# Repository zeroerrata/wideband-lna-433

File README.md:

<p align="center">
  <a href="https://zeroerrata.eu"><picture>
    <source media="(prefers-color-scheme: dark)" srcset="images/zeroerrata-logo-dark.png">
    
  </picture></a>
</p>

<h1 align="center">Wideband LNA 0.1-3 GHz with a 433 MHz SAW filter</h1>

<p align="center"><b>Low-noise amplifier for SDR receivers: SMA in, SMA out, 0.1-3 GHz, with a switchable 433.92 MHz SAW filter.</b></p>

## About

A small RF front end for software-defined radio receivers. A slide switch selects either the wideband path (0.1-3 GHz) or a 433.92 MHz SAW filter in front of the low-noise amplifier, so the same board serves as a general-purpose LNA and as a narrowband ISM-band preamplifier. It is powered from USB-C (5 V, power only) or through the RF output coax from the receiver's bias-tee (3.3-5 V); the two supplies are OR-ed by a Schottky pair, so it works on the bench and at the antenna mast.

The RF lines are 50-ohm grounded coplanar waveguide without solder mask on a 4-layer board with ENIG finish, fenced by ground vias, with tapered launches into edge-mount SMA connectors.

## Features

- Qorvo SPF5043Z LNA: NF 0.6-0.84 dB up to 2.2 GHz, gain about 23.5 dB at 0.1 GHz falling to about 10 dB at 3 GHz, OIP3 33-35 dBm
- Switchable RF360 B3760 SAW filter, 433.92 MHz: 320 kHz pass band (about 0.7 MHz at -3 dB), 1.9 dB insertion loss, with its matching network
- Two Skyworks AS179-92LF SPDT switches in series around the filter: about 50 dB leakage suppression, a LED for each mode
- Powered by USB-C 5 V or by bias-tee over the RF OUT coax (3.3-5 V)
- 50-ohm grounded coplanar waveguide (0.345 mm track, 0.3 mm gap, no solder mask), via fences, edge-launch SMA
- Hand-solderable: SOT-343 / SOT-363, 0402 on the RF path, 0603 elsewhere (the SAW needs hot air or a hot plate)

## Specifications

| | |
|---|---|
| Board | 56.0 x 34.0 mm, 4 copper layers, 1.6 mm |
| Finish | ENIG |
| Parts | 46 |
| Release | rev 3, 2026-11-27 |
| Frequency | 0.1-3 GHz (wideband) or 433.92 MHz (SAW) |
| RF connectors | 2 x edge-launch SMA, 50 ohm |
| Supply | USB-C 5 V or bias-tee 3.3-5 V on RF OUT |
| Stackup | 4 layers, 1.6 mm, outer copper 1 oz; RF on the top layer over a solid ground plane |

## Performance (simulated)

RF cascade of the whole board between 50-ohm ports: the routed lines on the real stackup, the switches, coupling and bias parts, the SMA launches. The LNA is modelled from its data-sheet curves, the SAW filter as a behavioural band-pass with its data-sheet insertion loss; a prediction, not a measurement.

| Path | Frequency | Gain | Noise figure | Input match (S11) |
|---|---|---|---|---|
| Wideband | 0.1 GHz | 22.3 dB | 1.25 dB | -10.0 dB |
| Wideband | 433.92 MHz | 19.6 dB | 1.34 dB | -13.2 dB |
| Wideband | 0.9 GHz | 16.6 dB | 1.51 dB | -13.9 dB |
| Wideband | 2.2 GHz | 9.7 dB | 2.17 dB | -14.0 dB |
| Wideband | 3 GHz | 7.0 dB | 2.72 dB | -13.3 dB |
| 433 MHz SAW | 433.77-434.07 MHz | 16.9-17.8 dB | 3.2-3.6 dB | -17.0 dB |

- Over part tolerances (Monte Carlo, 200 draws) every band check holds: wideband gain >= 6 dB, NF <= 3 dB, S11 <= -9 dB over 0.1-3 GHz; SAW path gain >= 14 dB (16.9 dB), NF <= 5.5 dB (3.6 dB) in the passband.
- Rejection of the SAW path relative to 433.92 MHz (data-sheet minimum of the filter): about 31 dB at 430 MHz, 21 dB at 437 MHz, 40-46 dB at 400 / 470 MHz, 51-55 dB from 868 MHz to 2.4 GHz, where the isolation of the two switches, not the filter, sets it.
- The data-sheet model of the LNA has no phase information; its stability factor dips below 1 near the edges of the sweep (mu 0.79), so check the stability with a VNA on the first boards.

## Renders

| Top | Bottom | Low |
|---|---|---|
|  |  |  |

## Files

| Folder | Contents |
|---|---|
| [`kicad/`](kicad) | KiCad 10 project: schematic, board, design rules, project libraries |
| [`docs/`](docs) | [schematic.pdf](docs/schematic.pdf), [board_layers.pdf](docs/board_layers.pdf), [assembly_top.pdf](docs/assembly_top.pdf) |
| [`fabrication/`](fabrication) | Gerber and drill files (zip), bill of materials, pick-and-place |
| [`images/`](images) | renders and copper layer pictures |
| [`analysis/`](analysis) | simulation and analysis results: bringup, dfm, retpath, sparam, thermal |

## Verification

- 50-ohm RF lines checked by a field solver: 12 RF nets at 50.0-51.6 ohm
- RF chain cascade (gain, noise figure, match) and Monte Carlo over part tolerances: see analysis/sparam
- Thermal map, return paths of the RF nets and a reflow balance check: see analysis/
- Every result is a prediction from design data; the board has not been measured unless stated.

## How to order

1. Upload `fabrication/gerbers_drill.zip` to your PCB fab; the stackup and finish are in the specifications above.
2. For assembly, use `fabrication/bom_jlcpcb.csv` and `fabrication/cpl_jlcpcb.csv` (JLCPCB format) or the KiCad-format `bom.csv` / `pos.csv`.
3. Check part stock and the footprints against the current data sheets before you order.

## Known issues

Found by the design review of this release; boards built from these files carry them:

- Reflow balance: from rev 3 the small ground pads connect through thermal reliefs; nine 0402 / 0603 parts remain at warning level in the reflow check, so use a profile with a 60-90 s soak at 150-180 C and inspect them.
- Parts: the B3760 SAW filter is not stocked by JLCPCB / LCSC (solder it by hand or consign it), and the AS179-92LF switches had little authorised stock in 2026. Check both before ordering.

## Notes

- The renders show the ZeroErrata house look; from rev 3 the fabrication package specifies it too: matte black solder mask, white silkscreen, ENIG.
- The SAW filter has its pads under the body: solder it with hot air or a hot plate.
- Rev 3 uses the B3760 SAW filter instead of the B3790 (obsolete at one distributor): 1.7 dB lower insertion loss and noise figure, a wider pass band (320 kHz instead of about 120 kHz) and less rejection within about 10 MHz of the carrier.

## Licence

Released under the [CERN Open Hardware Licence Version 2 - Permissive](LICENSE) (CERN-OHL-P-2.0): use, modify, make and sell it, also commercially. Provided as is, without warranty.

---

<p align="center">
  Designed by <a href="https://zeroerrata.eu"><b>ZeroErrata</b></a>: PCB design, verified before it is ordered.<br>
  <a href="https://zeroerrata.eu">zeroerrata.eu</a> · <a href="mailto:hello@zeroerrata.eu">hello@zeroerrata.eu</a>
</p>

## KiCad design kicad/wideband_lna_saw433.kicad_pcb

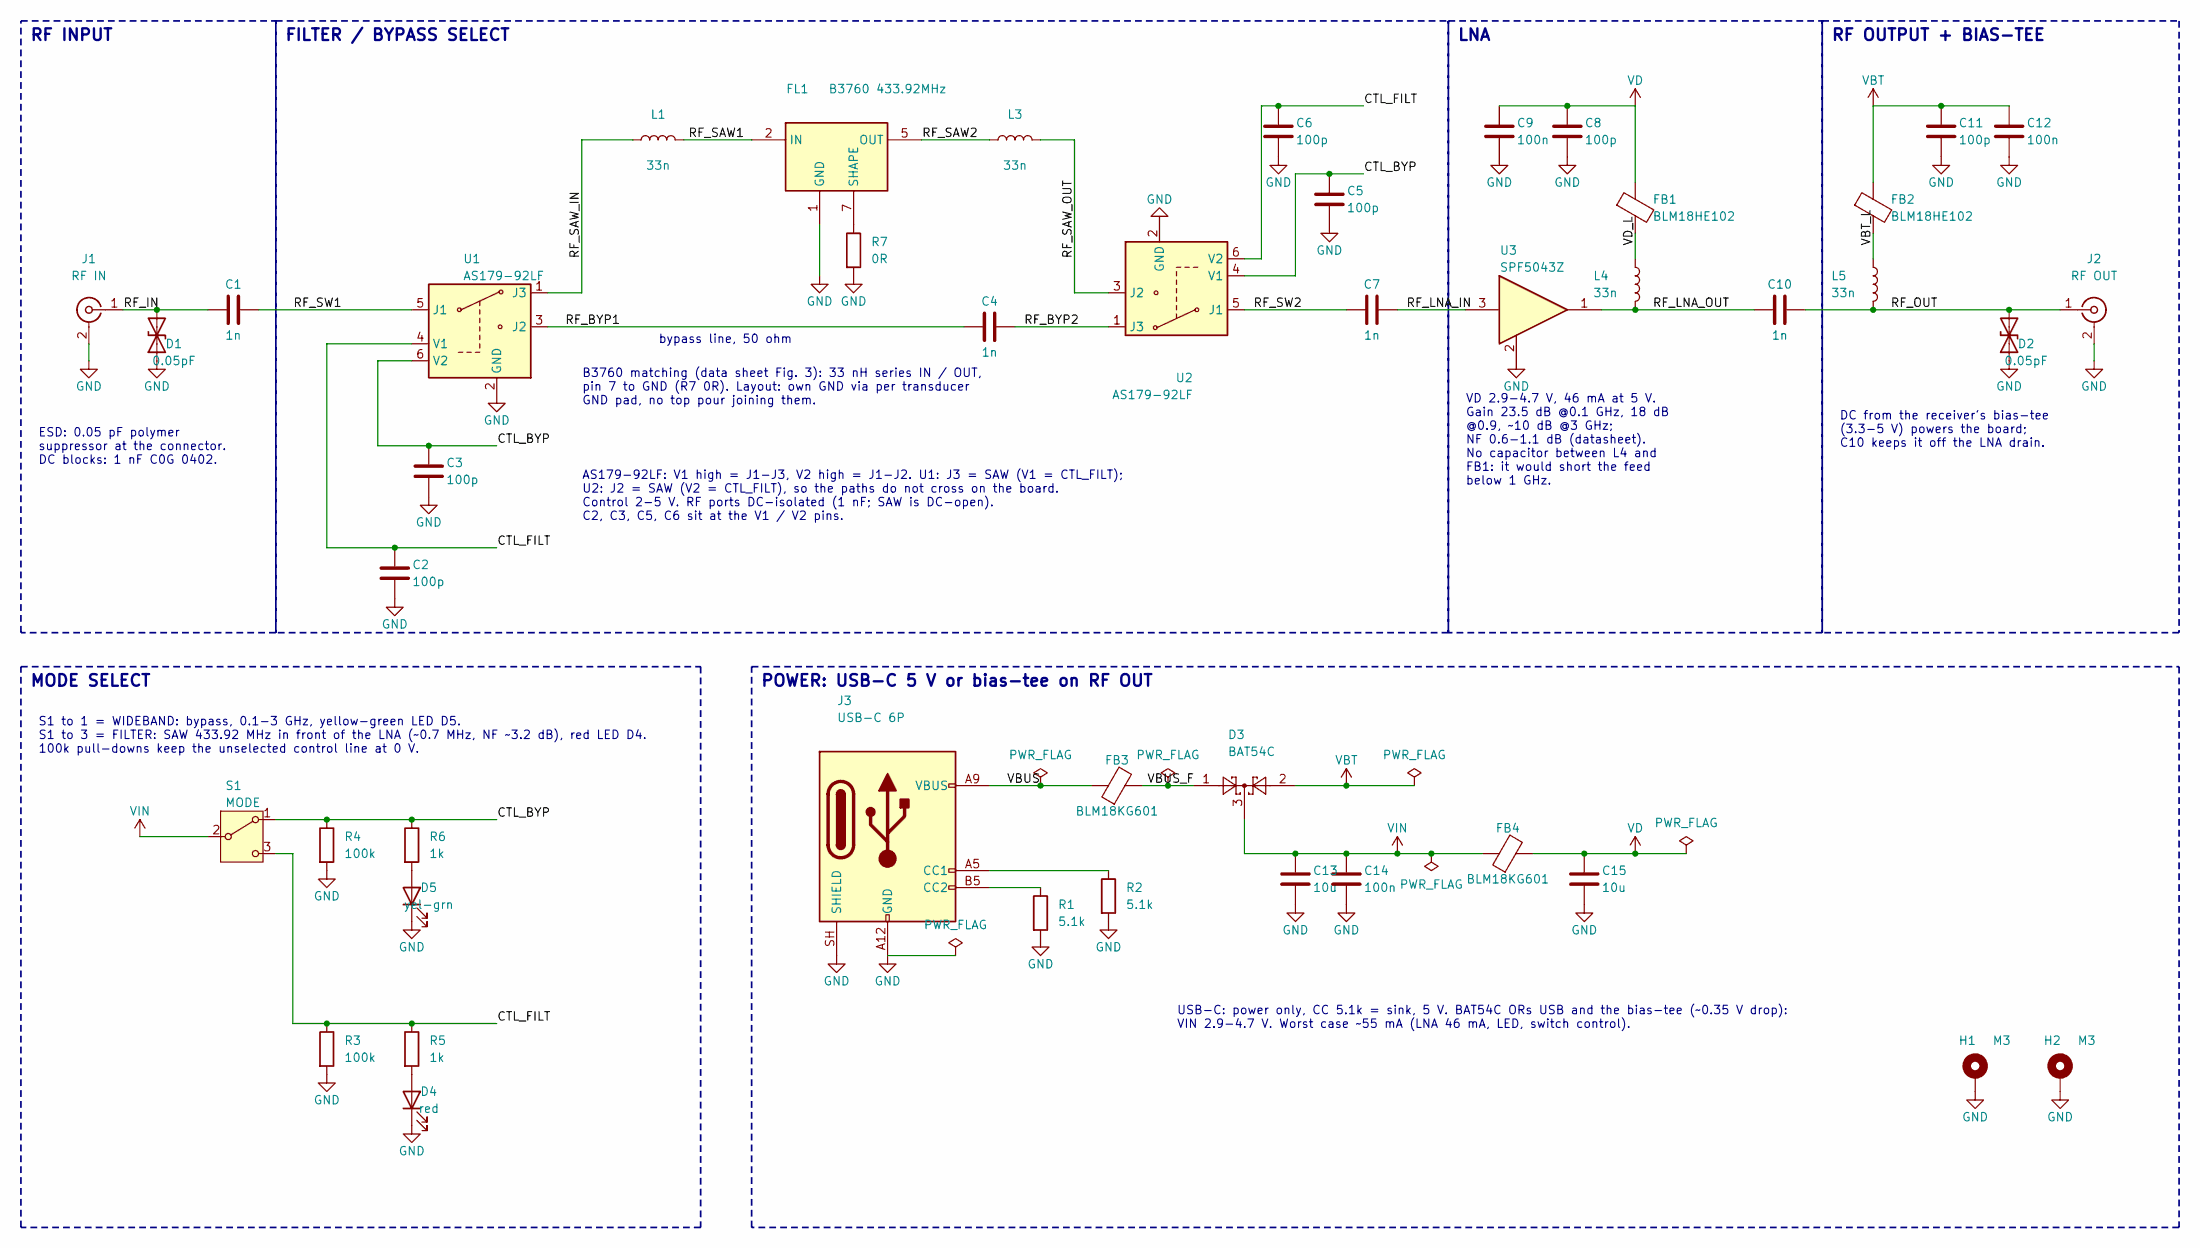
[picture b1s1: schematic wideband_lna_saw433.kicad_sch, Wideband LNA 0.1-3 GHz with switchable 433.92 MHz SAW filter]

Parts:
C1, C4, C7, C10: 1n; C_0402_1005Metric; MPN GRM1555C1H102JA01D; LCSC C76947
C2, C3, C5, C6, C8, C11: 100p; C_0402_1005Metric; MPN GRM1555C1H101JA01D; LCSC C77177
C9, C12, C14: 100n; C_0603_1608Metric; MPN CC0603KRX7R9BB104; LCSC C14663
C13, C15: 10u; C_0603_1608Metric; MPN CL10A106KP8NNNC; LCSC C19702
D1, D2: 0.05pF; D_0402_1005Metric; MPN BPESD0402-05ST; LCSC C316059
D3: BAT54C; SOT-23; MPN BAT54C,215; LCSC C37704
D4: red; LED_0603_1608Metric; MPN KT-0603R; LCSC C2286
D5: yel-grn; LED_0603_1608Metric; MPN XL-1608SYGC-06; LCSC C965805
FB1, FB2: BLM18HE102; L_0603_1608Metric; MPN BLM18HE102SN1D; LCSC C85828
FB3, FB4: BLM18KG601; L_0603_1608Metric; MPN BLM18KG601SN1D; LCSC C85833
FL1: B3760 433.92MHz; QCC8B_3.8x3.8mm; MPN B39431B3760Z810
H1, H2: M3; MountingHole_3.2mm_M3_Pad_Via
J1: RF IN; SMA_Molex_73251-1150_EdgeMount_PB; MPN 73251-1150; LCSC C841205
J2: RF OUT; SMA_Molex_73251-1150_EdgeMount_PB; MPN 73251-1150; LCSC C841205
J3: USB-C 6P; USB_C_Receptacle_ShouHan_TYPE-C-6P; MPN TYPE-C 6P; LCSC C456012
L1, L3, L4, L5: 33n; L_0402_1005Metric; MPN LQW15AN33NG00D; LCSC C113114
R1, R2: 5.1k; R_0603_1608Metric; MPN 0603WAF5101T5E; LCSC C23186
R3, R4: 100k; R_0603_1608Metric; MPN 0603WAF1003T5E; LCSC C25803
R5, R6: 1k; R_0603_1608Metric; MPN 0603WAF1001T5E; LCSC C21190
R7: 0R; L_0402_1005Metric; MPN 0402WGF0000TCE; LCSC C17168
S1: MODE; SW_SPDT_MSK12C02; MPN MSK12C02; LCSC C431540
U1, U2: AS179-92LF; SOT-363_SC-70-6; MPN AS179-92LF; LCSC C83422
U3: SPF5043Z; SOT-343_Qorvo_SPF5043Z; MPN SPF5043Z; LCSC C470902

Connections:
/CTL_BYP: C3.1, C5.1, R4.1, R6.1, S1.1 (A), U1.6 (V2), U2.4 (V1)
/CTL_FILT: C2.1, C6.1, R3.1, R5.1, S1.3 (C), U1.4 (V1), U2.6 (V2)
/RF_BYP1: C4.1, U1.3 (J2)
/RF_BYP2: C4.2, U2.1 (J3)
/RF_IN: C1.1, D1.2 (A2), J1.1 (In)
/RF_LNA_IN: C7.2, U3.3 (RFIN)
/RF_LNA_OUT: C10.1, L4.2, U3.1 (RFOUT/VD)
/RF_OUT: C10.2, D2.2 (A2), J2.1 (In), L5.2
/RF_SAW1: FL1.2 (IN), L1.2
/RF_SAW2: FL1.5 (OUT), L3.1
/RF_SAW_IN: L1.1, U1.1 (J3)
/RF_SAW_OUT: L3.2, U2.3 (J2)
/RF_SW1: C1.2, U1.5 (J1)
/RF_SW2: C7.1, U2.5 (J1)
/VBT_L: FB2.2, L5.1
/VBUS: FB3.1, J3.A9 (VBUS), J3.B9 (VBUS)
/VBUS_F: D3.1, FB3.2
/VD_L: FB1.2, L4.1
GND: C2.2, C3.2, C5.2, C6.2, C8.2, C9.2, C11.2, C12.2, C13.2, C14.2, C15.2, D1.1 (A1), D2.1 (A1), D4.1 (K), D5.1 (K), FL1.1 (GND), FL1.3 (GND), FL1.4 (GND), FL1.6 (GND), FL1.8 (GND), H1.1, H2.1, J1.2 (Ext), J2.2 (Ext), J3.A12 (GND), J3.B12 (GND), J3.SH (SHIELD), R1.2, R2.2, R3.2, R4.2, R7.2, U1.2 (GND), U2.2 (GND), U3.2 (GND), U3.4 (GND)
unnamed: D4.2 (A), R5.2
unnamed: D5.2 (A), R6.2
unnamed: FL1.7 (SHAPE), R7.1
unnamed: J3.A5 (CC1), R2.1
unnamed: J3.B5 (CC2), R1.1
VBT: C11.1, C12.1, D3.2, FB2.1
VD: C8.1, C9.1, C15.1, FB1.1, FB4.2
VIN: C13.1, C14.1, D3.3, FB4.1, S1.2 (B)

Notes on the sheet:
RF INPUT
ESD: 0.05 pF polymer suppressor at the connector. DC blocks: 1 nF C0G 0402.
FILTER / BYPASS SELECT
bypass line, 50 ohm
B3760 matching (data sheet Fig. 3): 33 nH series IN / OUT, pin 7 to GND (R7 0R). Layout: own GND via per transducer GND pad, no top pour joining them.
AS179-92LF: V1 high = J1-J3, V2 high = J1-J2. U1: J3 = SAW (V1 = CTL_FILT); U2: J2 = SAW (V2 = CTL_FILT), so the paths do not cross on the board. Control 2-5 V. RF ports DC-isolated (1 nF; SAW is DC-open). C2, C3, C5, C6 sit at the V1 / V2 pins.
LNA
VD 2.9-4.7 V, 46 mA at 5 V. Gain 23.5 dB @0.1 GHz, 18 dB @0.9, ~10 dB @3 GHz; NF 0.6-1.1 dB (datasheet). No capacitor between L4 and FB1: it would short the feed below 1 GHz.
RF OUTPUT + BIAS-TEE
DC from the receiver's bias-tee (3.3-5 V) powers the board; C10 keeps it off the LNA drain.
MODE SELECT
S1 to 1 = WIDEBAND: bypass, 0.1-3 GHz, yellow-green LED D5. S1 to 3 = FILTER: SAW 433.92 MHz in front of the LNA (~0.7 MHz, NF ~3.2 dB), red LED D4. 100k pull-downs keep the unselected control line at 0 V.
POWER: USB-C 5 V or bias-tee on RF OUT
USB-C: power only, CC 5.1k = sink, 5 V. BAT54C ORs USB and the bias-tee (~0.35 V drop): VIN 2.9-4.7 V. Worst case ~55 mA (LNA 46 mA, LED, switch control).

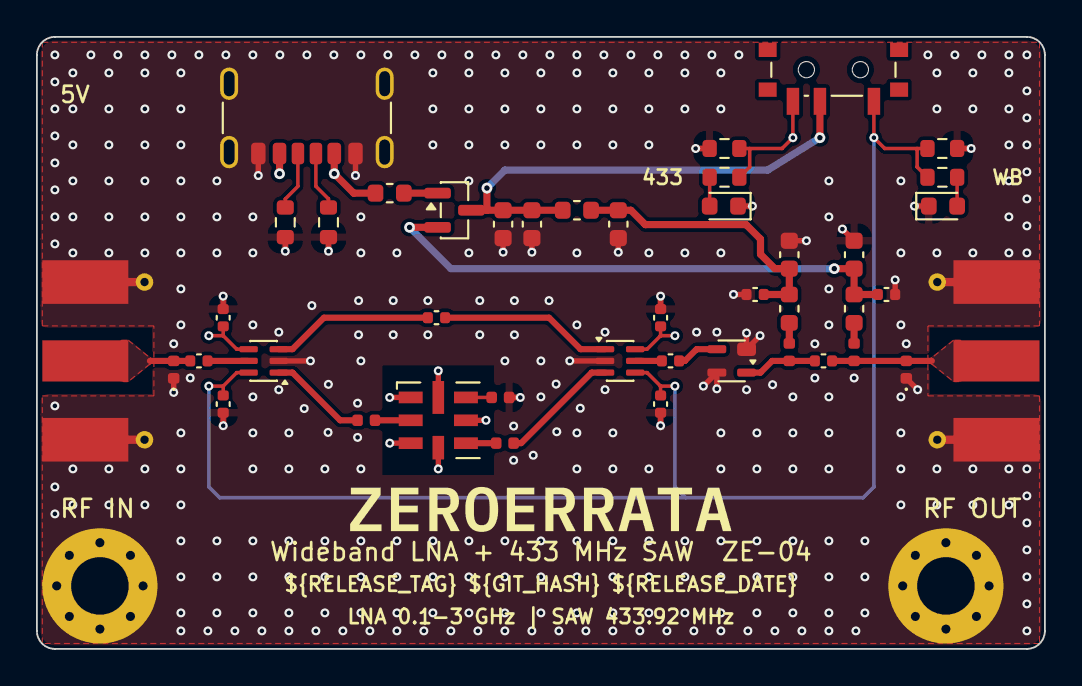
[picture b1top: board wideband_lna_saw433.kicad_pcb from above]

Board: 4 copper layers, 56.0 x 34.0 mm, 46 parts (0 on the bottom side), 27 nets.

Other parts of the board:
LOGO1: ZeroErrata logo; ZeroErrata_wordmark_2.5mm

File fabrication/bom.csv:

"Designator","Value","Footprint","Quantity","Manufacturer","MPN","LCSC Part #"
"C1,C4,C7,C10","1n","Capacitor_SMD:C_0402_1005Metric","4","Murata","GRM1555C1H102JA01D","C76947"
"C2,C3,C5,C6,C8,C11","100p","Capacitor_SMD:C_0402_1005Metric","6","Murata","GRM1555C1H101JA01D","C77177"
"C9,C12,C14","100n","Capacitor_SMD:C_0603_1608Metric","3","YAGEO","CC0603KRX7R9BB104","C14663"
"C13,C15","10u","Capacitor_SMD:C_0603_1608Metric","2","Samsung","CL10A106KP8NNNC","C19702"
"D1,D2","0.05pF","Diode_SMD:D_0402_1005Metric","2","BORN","BPESD0402-05ST","C316059"
"D3","BAT54C","Package_TO_SOT_SMD:SOT-23","1","Nexperia","BAT54C,215","C37704"
"D4","red","LED_SMD:LED_0603_1608Metric","1","KENTO","KT-0603R","C2286"
"D5","yel-grn","LED_SMD:LED_0603_1608Metric","1","XINGLIGHT","XL-1608SYGC-06","C965805"
"FB1,FB2","BLM18HE102","Inductor_SMD:L_0603_1608Metric","2","Murata","BLM18HE102SN1D","C85828"
"FB3,FB4","BLM18KG601","Inductor_SMD:L_0603_1608Metric","2","Murata","BLM18KG601SN1D","C85833"
"FL1","B3760 433.92MHz","lna433:QCC8B_3.8x3.8mm","1","RF360 (Qualcomm/TDK)","B39431B3760Z810",""
"J1","RF IN","lna433:SMA_Molex_73251-1150_EdgeMount_PB","1","Molex","73251-1150","C841205"
"J2","RF OUT","lna433:SMA_Molex_73251-1150_EdgeMount_PB","1","Molex","73251-1150","C841205"
"J3","USB-C 6P","lna433:USB_C_Receptacle_ShouHan_TYPE-C-6P","1","SHOU HAN","TYPE-C 6P","C456012"
"L1,L3-L5","33n","Inductor_SMD:L_0402_1005Metric","4","Murata","LQW15AN33NG00D","C113114"
"R1,R2","5.1k","Resistor_SMD:R_0603_1608Metric","2","UNI-ROYAL","0603WAF5101T5E","C23186"
"R3,R4","100k","Resistor_SMD:R_0603_1608Metric","2","UNI-ROYAL","0603WAF1003T5E","C25803"
"R5,R6","1k","Resistor_SMD:R_0603_1608Metric","2","UNI-ROYAL","0603WAF1001T5E","C21190"
"R7","0R","Inductor_SMD:L_0402_1005Metric","1","UNI-ROYAL","0402WGF0000TCE","C17168"
"S1","MODE","lna433:SW_SPDT_MSK12C02","1","SHOU HAN","MSK12C02","C431540"
"U1,U2","AS179-92LF","Package_TO_SOT_SMD:SOT-363_SC-70-6","2","Skyworks","AS179-92LF","C83422"
"U3","SPF5043Z","lna433:SOT-343_Qorvo_SPF5043Z","1","Qorvo","SPF5043Z","C470902"

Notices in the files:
parts and their libraries:
LICENSE: CERN-OHL-S-2.0
